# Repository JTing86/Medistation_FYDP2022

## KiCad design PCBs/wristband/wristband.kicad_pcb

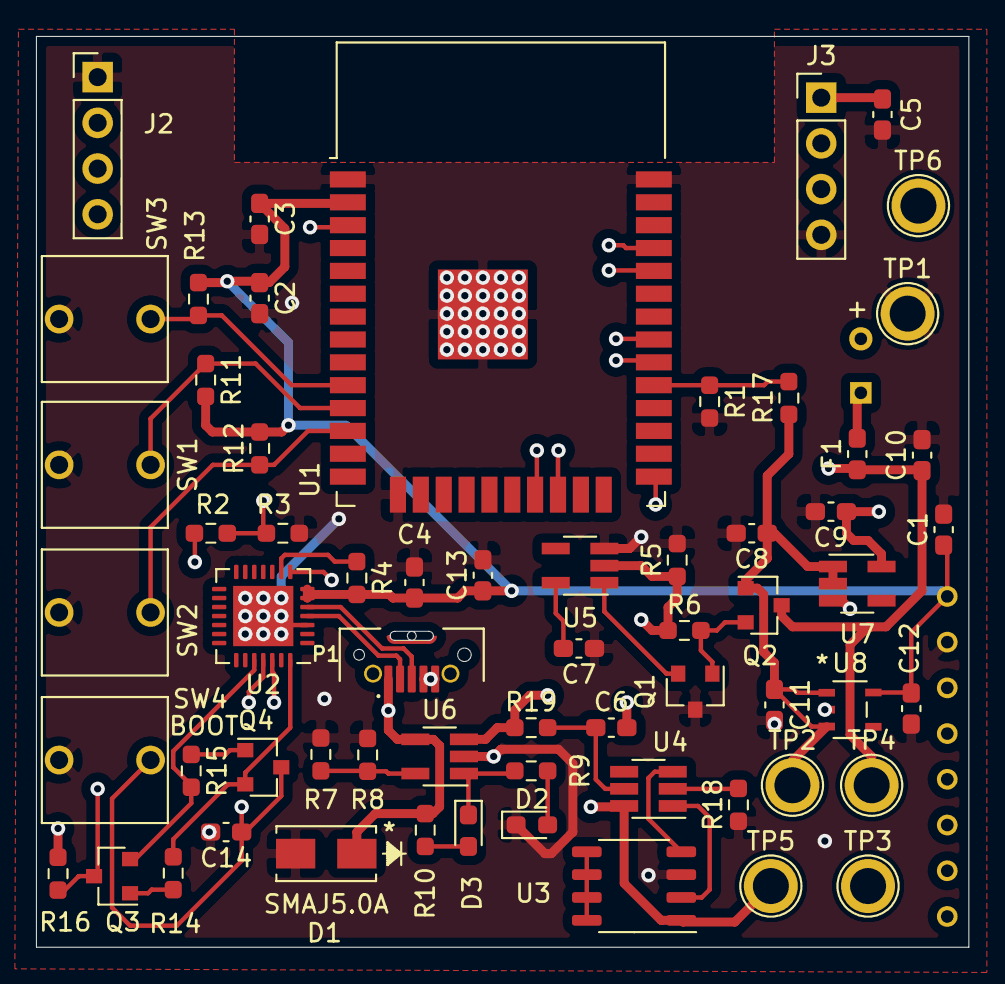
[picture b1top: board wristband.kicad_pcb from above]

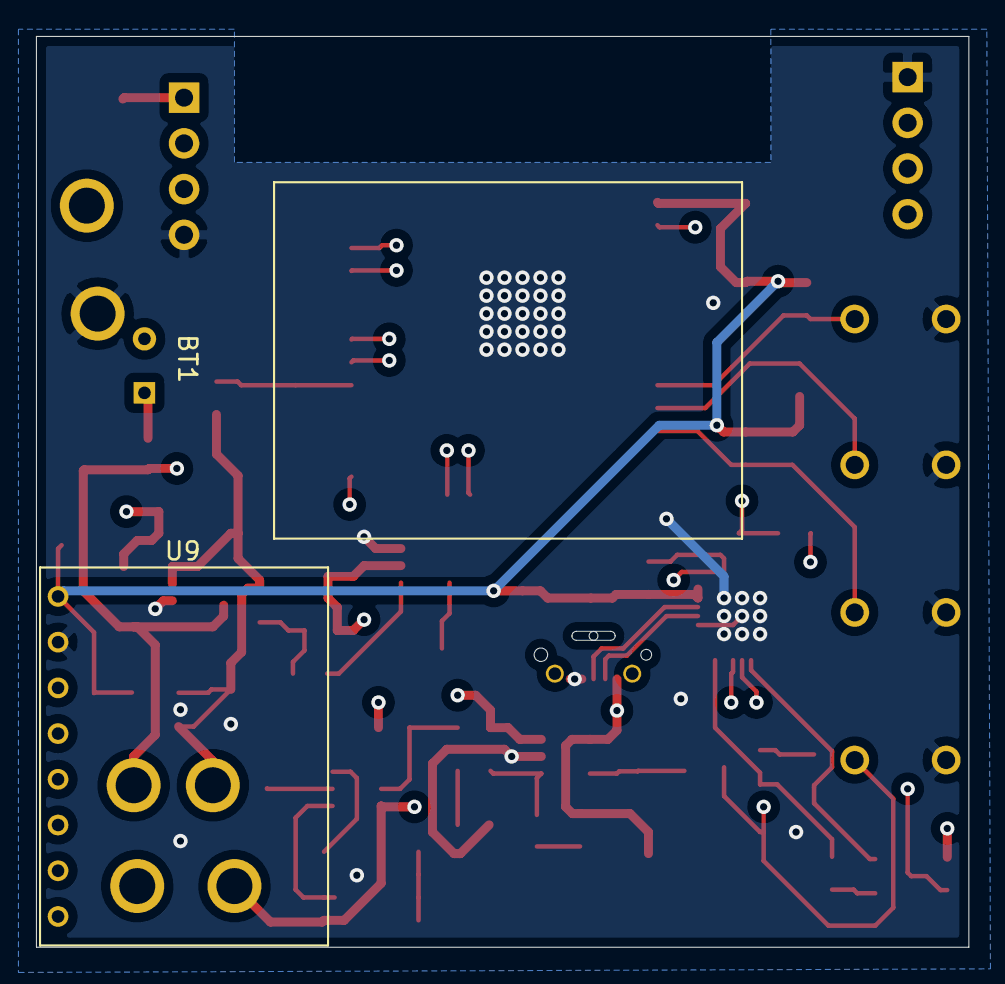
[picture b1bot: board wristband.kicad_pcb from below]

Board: 4 copper layers, 51.8 x 50.6 mm, 64 parts (2 on the bottom side), 40 nets.

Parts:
BT1: 3.7V; battery
C1: CP1_Small; C_0603_1608Metric_Pad1.08x0.95mm_HandSolder
C2: 10 uF; C_0603_1608Metric_Pad1.08x0.95mm_HandSolder
C3, C5, C13, C14: 0.1 uF; C_0603_1608Metric_Pad1.08x0.95mm_HandSolder
C4: 4.7 uF; C_0603_1608Metric_Pad1.08x0.95mm_HandSolder
C6: 0.1u; C_0603_1608Metric_Pad1.08x0.95mm_HandSolder
C7: 1.8 nF; C_0603_1608Metric_Pad1.08x0.95mm_HandSolder
C8, C9, C11, C12: 1 uF; C_0603_1608Metric_Pad1.08x0.95mm_HandSolder
C10: 1.0 uF; C_0603_1608Metric_Pad1.08x0.95mm_HandSolder
D1: SMAJ5.0A
D2: GREEN_LED; LED_0603_1608Metric_Pad1.05x0.95mm_HandSolder
D3: BLUE_LED; LED_0603_1608Metric_Pad1.05x0.95mm_HandSolder
F1: 300 mA; Fuse_0603_1608Metric_Pad1.05x0.95mm_HandSolder
J2: HLTH_2; PinHeader_1x04_P2.54mm_Vertical
J3: HLTH_1; PinHeader_1x04_P2.54mm_Vertical
P1: KMMVX-SMT-BS-BTR; KYCON_KMMVX-SMT-BS-BTR
Q1: Q_NMOS_DGS; SOT-23
Q2: Q_PMOS_DGS; SOT-23
Q3, Q4: Q_NPN_BEC; SOT-23
R1: 20k; R_0603_1608Metric_Pad0.98x0.95mm_HandSolder
R2: 24k; R_0603_1608Metric_Pad0.98x0.95mm_HandSolder
R3: 47k; R_0603_1608Metric_Pad0.98x0.95mm_HandSolder
R4: 2k; R_0603_1608Metric_Pad0.98x0.95mm_HandSolder
R5: 5M; R_0603_1608Metric_Pad0.98x0.95mm_HandSolder
R6: 100K; R_0603_1608Metric_Pad0.98x0.95mm_HandSolder
R7: 20K; R_0603_1608Metric_Pad0.98x0.95mm_HandSolder
R8, R14, R15, R16: 10K; R_0603_1608Metric_Pad0.98x0.95mm_HandSolder
R9, R10, R11, R12, R13: 1K; R_0603_1608Metric_Pad0.98x0.95mm_HandSolder
R17: 15k; R_0603_1608Metric_Pad0.98x0.95mm_HandSolder
R18: 1k; R_0603_1608Metric_Pad0.98x0.95mm_HandSolder
R19: 100; R_0603_1608Metric_Pad0.98x0.95mm_HandSolder
SW1, SW2, SW3, SW4: SW_SPST; button
TP1, TP2, TP3, TP4, TP5, TP6: TestPoint; TestPoint_Plated_Hole_D2.0mm
U1: ESP32-WROOM-32
U2: CP2102N-A01-GQFN28; QFN-28-1EP_5x5mm_P0.5mm_EP3.35x3.35mm
U3: DMG9926USD; SOP-8_3.9x4.9mm_P1.27mm
U4: DW01; SOT-23-6_Handsoldering
U5: S-1009N341-M5T1U; SOT-23-5_HandSoldering
U6: MCP73831-2-OT; SOT-23-5_HandSoldering
U7: ADP151; SOT-23-5_HandSoldering
U8: BU33SD5WG; BU33SD5WG-TR
U9: MPU6050

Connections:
+1V8: C5.1, C9.1, J3.1, TP3.1, U7.5
+3V3: C1.1, C2.1, C3.1, C4.1, C12.1, C13.1, R4.2, R11.2, R12.2, R13.2, R16.1, TP6.1, U1.2, U2.6, U2.7, U8.5, U9.1
+BATT: C10.1, F1.1, Q2.3, R5.1, R6.1, R19.1, TP4.1, U5.2, U6.3
-BATT: BT1.2, C6.2, TP5.1, U3.1, U4.6
/BMS/D+: P1.2, U2.4
/BMS/D-: P1.3, U2.5
/BMS/VBUS: D1.1, P1.1, R2.2, R10.1, U6.4
ACC_INT: U1.30, U9.8
BATT_OUT: C8.1, C11.1, Q2.1, R17.1, TP2.1, U7.1, U7.2, U8.1, U8.3
DTR: Q4.2, R14.2, U2.28
EN: Q3.3, R16.2, U1.3
GND: C1.2, C2.2, C3.2, C4.2, C5.2, C7.1, C8.2, C9.2, C10.2, C11.2, C12.2, C13.2, C14.2, D1.2, D2.1, J2.1, J3.4, P1.4, P1.5, Q1.3, R1.2, R3.1, R5.2, R7.2, R8.2, R18.1, SW1.1, SW2.1, SW3.1, SW4.1, TP1.1, U1.1, U1.15, U1.38, U1.39, U2.3, U2.29, U3.3, U5.3, U6.2, U7.3, U8.2, U9.2
HLTH_INT: J2.4, U1.31
IO_0: C14.1, Q4.3, SW4.2, U1.25
unnamed: BT1.1, F1.2
unnamed: C6.1, R19.2, U4.5
unnamed: C7.2, U5.5
unnamed: D2.2, R9.2
unnamed: D3.1, R9.1, U6.1
unnamed: D3.2, R10.2
unnamed: Q1.1, Q2.2, R6.2
unnamed: Q1.2, U5.1
unnamed: Q3.1, R14.1
unnamed: Q4.1, R15.1
unnamed: R1.1, R17.2, U1.29
unnamed: R2.1, R3.2, U2.8
unnamed: R4.1, U2.9
unnamed: R7.1, R8.1, U6.5
unnamed: R18.2, U4.2
unnamed: U3.2, U4.1
unnamed: U3.4, U4.3
unnamed: U3.5, U3.6, U3.7, U3.8
PB_1: R13.1, SW3.2, U1.10
PB_2: R11.1, SW1.2, U1.11
PB_3: R12.1, SW2.2, U1.12
RTS: Q3.2, R15.2, U2.24
RXD: U1.35, U2.25
SCL: J3.3, U1.22, U9.4
SDA: J3.2, U1.21, U9.3
TXD: U1.34, U2.26

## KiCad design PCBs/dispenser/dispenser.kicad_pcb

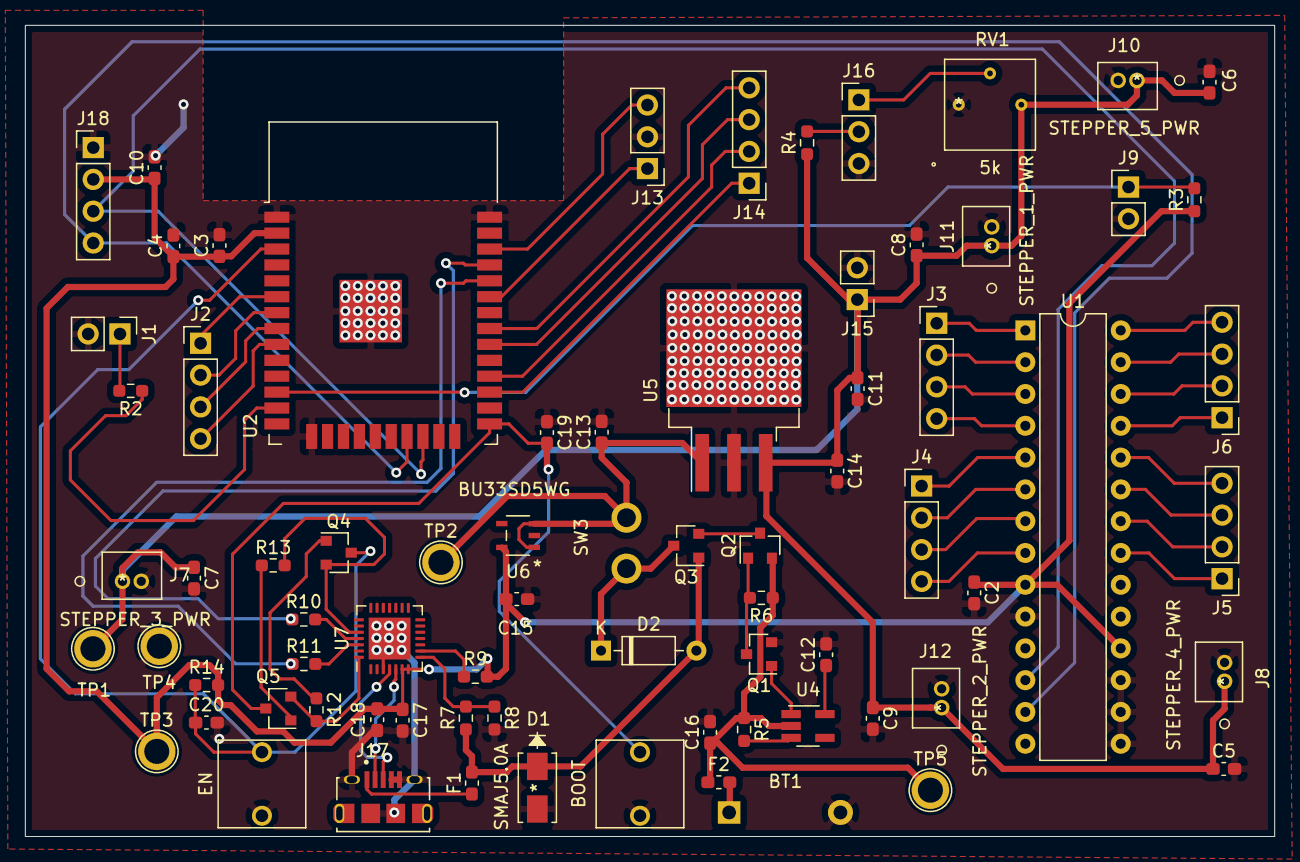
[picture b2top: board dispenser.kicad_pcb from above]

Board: 2 copper layers, 99.8 x 64.8 mm, 75 parts (0 on the bottom side), 61 nets.

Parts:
BT1: AA_holder; battery_holder
C2, C5, C6, C7, C8, C9: 1 uF; C_0603_1608Metric_Pad1.08x0.95mm_HandSolder
C3, C16: 10 uF; C_0603_1608Metric_Pad1.08x0.95mm_HandSolder
C4, C10, C14, C18, C19, C20: 0.1 uF; C_0603_1608Metric_Pad1.08x0.95mm_HandSolder
C11, C15: 10uF; C_0603_1608Metric_Pad1.08x0.95mm_HandSolder
C12: 1.8 nF; C_0603_1608Metric_Pad1.08x0.95mm_HandSolder
C13: 0.33 uF; C_0603_1608Metric_Pad1.08x0.95mm_HandSolder
C17: 4.7 uF; C_0603_1608Metric_Pad1.08x0.95mm_HandSolder
D1: SMAJ5.0A
D2: D; D_DO-35_SOD27_P7.62mm_Horizontal
F1, F2: 1.5A fuse; Fuse_0603_1608Metric_Pad1.05x0.95mm_HandSolder
J1: BUZZ_CONN; PinHeader_1x02_P2.54mm_Vertical
J2: STEPPER_5; PinHeader_1x04_P2.54mm_Vertical
J3: STEPPER_1; PinHeader_1x04_P2.54mm_Vertical
J4: STEPPER_2; PinHeader_1x04_P2.54mm_Vertical
J5: STEPPER_3; PinHeader_1x04_P2.54mm_Vertical
J6: STEPPER_4; PinHeader_1x04_P2.54mm_Vertical
J7: STEPPER_3_PWR; B2B-ZRLFSN
J8: STEPPER_4_PWR; B2B-ZRLFSN
J9: PB_conn; PinHeader_1x02_P2.54mm_Vertical
J10: STEPPER_5_PWR; B2B-ZRLFSN
J11: STEPPER_1_PWR; B2B-ZRLFSN
J12: STEPPER_2_PWR; B2B-ZRLFSN
J13: LCD_conn_1; PinHeader_1x03_P2.54mm_Vertical
J14: LCD_conn_2; PinHeader_1x04_P2.54mm_Vertical
J15: LCD_conn_3; PinHeader_1x02_P2.54mm_Vertical
J16: LCD_conn_4; PinHeader_1x03_P2.54mm_Vertical
J17: USB_B_Micro; AMPHENOL_10118194-0001LF
J18: force_sense_conn; PinHeader_1x04_P2.54mm_Vertical
Q1: Q_NMOS_GSD; SOT-23
Q2, Q3: Q_PMOS_GSD; SOT-23
Q4, Q5: Q_NPN_BEC; SOT-23
R2: 100; R_0603_1608Metric_Pad0.98x0.95mm_HandSolder
R3: 1K; R_0603_1608Metric_Pad0.98x0.95mm_HandSolder
R4: 330; R_0603_1608Metric_Pad0.98x0.95mm_HandSolder
R5: 5M; R_0603_1608Metric_Pad0.98x0.95mm_HandSolder
R6: 100K; R_0603_1608Metric_Pad0.98x0.95mm_HandSolder
R7: 24k; R_0603_1608Metric_Pad0.98x0.95mm_HandSolder
R8: 47k; R_0603_1608Metric_Pad0.98x0.95mm_HandSolder
R9, R10, R11: 2k; R_0603_1608Metric_Pad0.98x0.95mm_HandSolder
R12, R13, R14: 10k; R_0603_1608Metric_Pad0.98x0.95mm_HandSolder
RV1: 5k; CT-6EP501
SW1: BOOT; button
SW2: EN; button
SW3: PWR_SWITCH; M2011S2A1W01
TP1, TP2, TP3, TP4, TP5: TestPoint; TestPoint_Plated_Hole_D2.0mm
U1: MCP23017_SP; DIP-28_W7.62mm
U2: ESP32-WROOM-32
U4: S-1009N34I-M5T1U; SOT-23-5_HandSoldering
U5: uA7805; TO-263-3_TabPin2
U6: BU33SD5WG; BU33SD5WG-TR
U7: CP2102N-A01-GQFN28; QFN-28-1EP_5x5mm_P0.5mm_EP3.35x3.35mm

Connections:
+3V3: C2.1, C3.1, C4.1, C10.1, C15.1, C17.1, C18.1, J18.2, R3.1, R9.2, R14.2, TP3.1, U1.9, U1.18, U2.2, U6.5, U7.6, U7.7
+5V: C5.1, C6.1, C7.1, C8.1, C9.1, C11.1, C14.1, J7.1, J8.1, J10.1, J11.1, J12.1, J15.1, R4.1, RV1.3, TP1.1, U5.3
+BATT: C16.1, F2.1, Q2.2, R5.1, R6.1, TP5.1, U4.2
/UART/D+: J17.3, U7.4
/UART/D-: J17.2, U7.5
/UART/VBUS: D1.1, D2.2, F1.2, Q3.1, R7.1
BUZZ_PWM: R2.1, U2.13
DTR: Q5.2, R12.2, U7.28
EN: C20.1, Q4.3, R14.1, SW2.2, U2.3
GND: BT1.2, C2.2, C3.2, C4.2, C5.2, C6.2, C7.2, C8.2, C9.2, C10.2, C11.2, C12.2, C13.2, C14.2, C15.2, C16.2, C17.2, C18.2, C19.1, C20.2, D1.2, J1.2, J7.2, J8.2, J9.2, J10.2, J11.2, J12.2, J13.2, J15.2, J16.3, J17.4, J17.5, J17.6, J18.1, Q1.2, R8.2, RV1.1, SW1.1, SW2.1, TP4.1, U1.10, U1.15, U1.16, U1.17, U2.1, U2.15, U2.38, U2.39, U5.2, U6.2, U7.3, U7.29
IO_0: C19.2, Q5.3, SW1.2, U2.25
LCD_D4: J14.1, U2.27
LCD_D5: J14.2, U2.28
LCD_D6: J14.3, U2.30
LCD_D7: J14.4, U2.31
LCD_ENABLE: J13.1, U2.33
LCD_RS: J13.3, U2.36
unnamed: BT1.1, F2.2
unnamed: C12.1, U4.5
unnamed: D2.1, Q3.3, SW3.1
unnamed: F1.1, J17.1
unnamed: J1.1, R2.2
unnamed: J16.1, RV1.2
unnamed: J16.2, R4.2
unnamed: Q1.1, U4.1
unnamed: Q1.3, Q2.1, R6.2
unnamed: Q2.3, Q3.2
unnamed: Q4.1, R12.1
unnamed: Q5.1, R13.1
unnamed: R5.2, U4.3
unnamed: R7.2, R8.1, U7.8
unnamed: R9.1, U7.9
unnamed: R10.2, U7.25
unnamed: R11.2, U7.26
PB: J9.1, R3.2, U2.12
POWER: C13.1, SW3.2, TP2.1, U5.1, U6.1, U6.3
RTS: Q4.2, R13.2, U7.24
RXD: R10.1, U2.35
SCL: J18.3, U1.12, U2.22
SDA: J18.4, U1.13, U2.21
STEPPER_1_1: J3.1, U1.1
STEPPER_1_2: J3.2, U1.2
STEPPER_1_3: J3.3, U1.3
STEPPER_1_4: J3.4, U1.4
STEPPER_2_1: J4.1, U1.5
STEPPER_2_2: J4.2, U1.6
STEPPER_2_3: J4.3, U1.7
STEPPER_2_4: J4.4, U1.8
STEPPER_3_1: J5.1, U1.21
STEPPER_3_2: J5.2, U1.22
STEPPER_3_3: J5.3, U1.23
STEPPER_3_4: J5.4, U1.24
STEPPER_4_1: J6.1, U1.25
STEPPER_4_2: J6.2, U1.26
STEPPER_4_3: J6.3, U1.27
STEPPER_4_4: J6.4, U1.28
STEPPER_5_1: J2.1, U2.6
STEPPER_5_2: J2.2, U2.7
STEPPER_5_3: J2.3, U2.8
STEPPER_5_4: J2.4, U2.9
TXD: R11.1, U2.34

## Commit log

2021-04-21 creating initial repo structure
2021-05-10 generated initial STM32 board code
2021-05-10 organized firmware structure
2021-05-10 deleted extra files
2021-05-13 initial commit of android app
2021-05-14 added basic search functionality
2021-05-28 Added navigation buttons at bottom of screen
2021-06-06 Testing
2021-06-15 Added Button
2021-06-15 Added Button to add symptom to database
2021-06-16 Got Database Working
2021-06-18 Able to create a new user on database
2021-06-18 can new symptoms to an existing user, add timestamp to existing symptoms and retrieve all time stamp of any symptom
2021-06-23 Minor changes after June 21st meeting
2021-09-21 commit before I mess with things
2021-10-05 3 hours of work and 3 textviews....
2021-10-05 trying to write helper function to access database
2021-10-06 Oct6th triggering
2021-10-07 oct6th ProfileFragment work in progress
2021-10-09 on other laptop
2021-10-10 almost done profile fragment
2021-10-11 made drop down menu work in profile fragment
2021-10-11 profile fragment almost done
2021-10-13 profile fragment completed
2021-10-14 profile fragment completed with one bug fixed
2021-10-16 created wristbandsetting fragment
2021-10-17 sett up wristbandsetting fragment
2021-10-17 wristband setting fragment complete
2021-10-18 working on dispenser fragment
2021-10-19 debugging dispenser fragment
2021-10-19 figured out bug regarding calibration section
2021-10-19 completed dispenser fragment
2021-10-21 medication schedule work in progress
2021-10-23 got medication fragment working (work in progress)
2021-10-24 changed structure of medication fragment
2021-10-26 backend of medicationfragment
2021-10-28 commit so I can work on desktop
2021-10-30 finished medication fragment (need to check for edge cases)
2021-11-02 just going through TODO list and fixing up code
2021-12-01 got MQTT working Dec 1st 2021
2021-12-17 added more MQTT functionalities
2021-12-21 heart rate, temp, firebase DB stuff
2021-12-21 cleaned up stuff
2021-12-21 missed some comments
2021-12-21 need to store current code to debug, navigation bar issue
2021-12-24 modified ProfileFragment and DeviceFragment based on new MQTT and db structure
2021-12-25 fixed up ProfileFragment, wristbandsettingFragment and dispenserSettingsFragment
2021-12-25 commit before fixing bug regarding saving pill schedule to DB
2021-12-25 fixed schedule being saved to database bug
2021-12-26 bit of tidying up
2021-12-27 added more functionalities to the HomeFragment
2021-12-29 added health and device status to the HomeFragment
2022-01-01 home_fragment work in progress
2022-01-15 home_fragment completed but did not check for bugs
2022-01-20 completed home_fragment
2022-01-20 added some graph stuff
2022-01-28 added graph stuff (heart rate)
2022-02-04 fixup! added graph stuff (heart rate)
2022-02-05 sleep quality creating new data
2022-02-07 added sleep quality functionality
2022-02-12 minor fixes
2022-02-26 minor fixes to graph function
2022-02-27 working on desktop
2022-02-28 basically all the code
2022-02-28 after integration, need few more fixes
2022-03-01 added motor stuff, changed I2c, got rid of pushing incomplete data
2022-03-01 added libraries
2022-03-01 added push sleep quality
2022-03-01 made a REST library
2022-03-01 working ESP initial integrating
2022-03-04 added PCBs
2022-03-08 need to add button to home fragment (work in progress)
2022-03-09 working needs calibration
2022-03-09 debugging MedicationFragment
2022-03-10 fixed schedule bug
2022-03-10 major changes incoming
2022-03-11 working stable 3D visual
2022-03-11 pre-integration
2022-03-11 working sleep algo
2022-03-11 improved working algo
2022-03-11 updated wristband things
2022-03-11 save before integrating
2022-03-11 added Date library
2022-03-11 integrated JT's code
2022-03-11 working integration code
2022-03-11 potentially complete
2022-03-11 demo version
2022-03-14 added MPU lib
2022-03-14 latest wristband code
2022-03-15 working in Nathaniel house

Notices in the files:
parts and their libraries:
Copyright 2021 Accelerated Designs. All rights reserved.
